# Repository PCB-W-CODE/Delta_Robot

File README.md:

# Delta_Robot
Design, simulation, and prototyping of a Delta robot with inverse kinematics, 3D printing, stepper motors, and manual control via joystick.

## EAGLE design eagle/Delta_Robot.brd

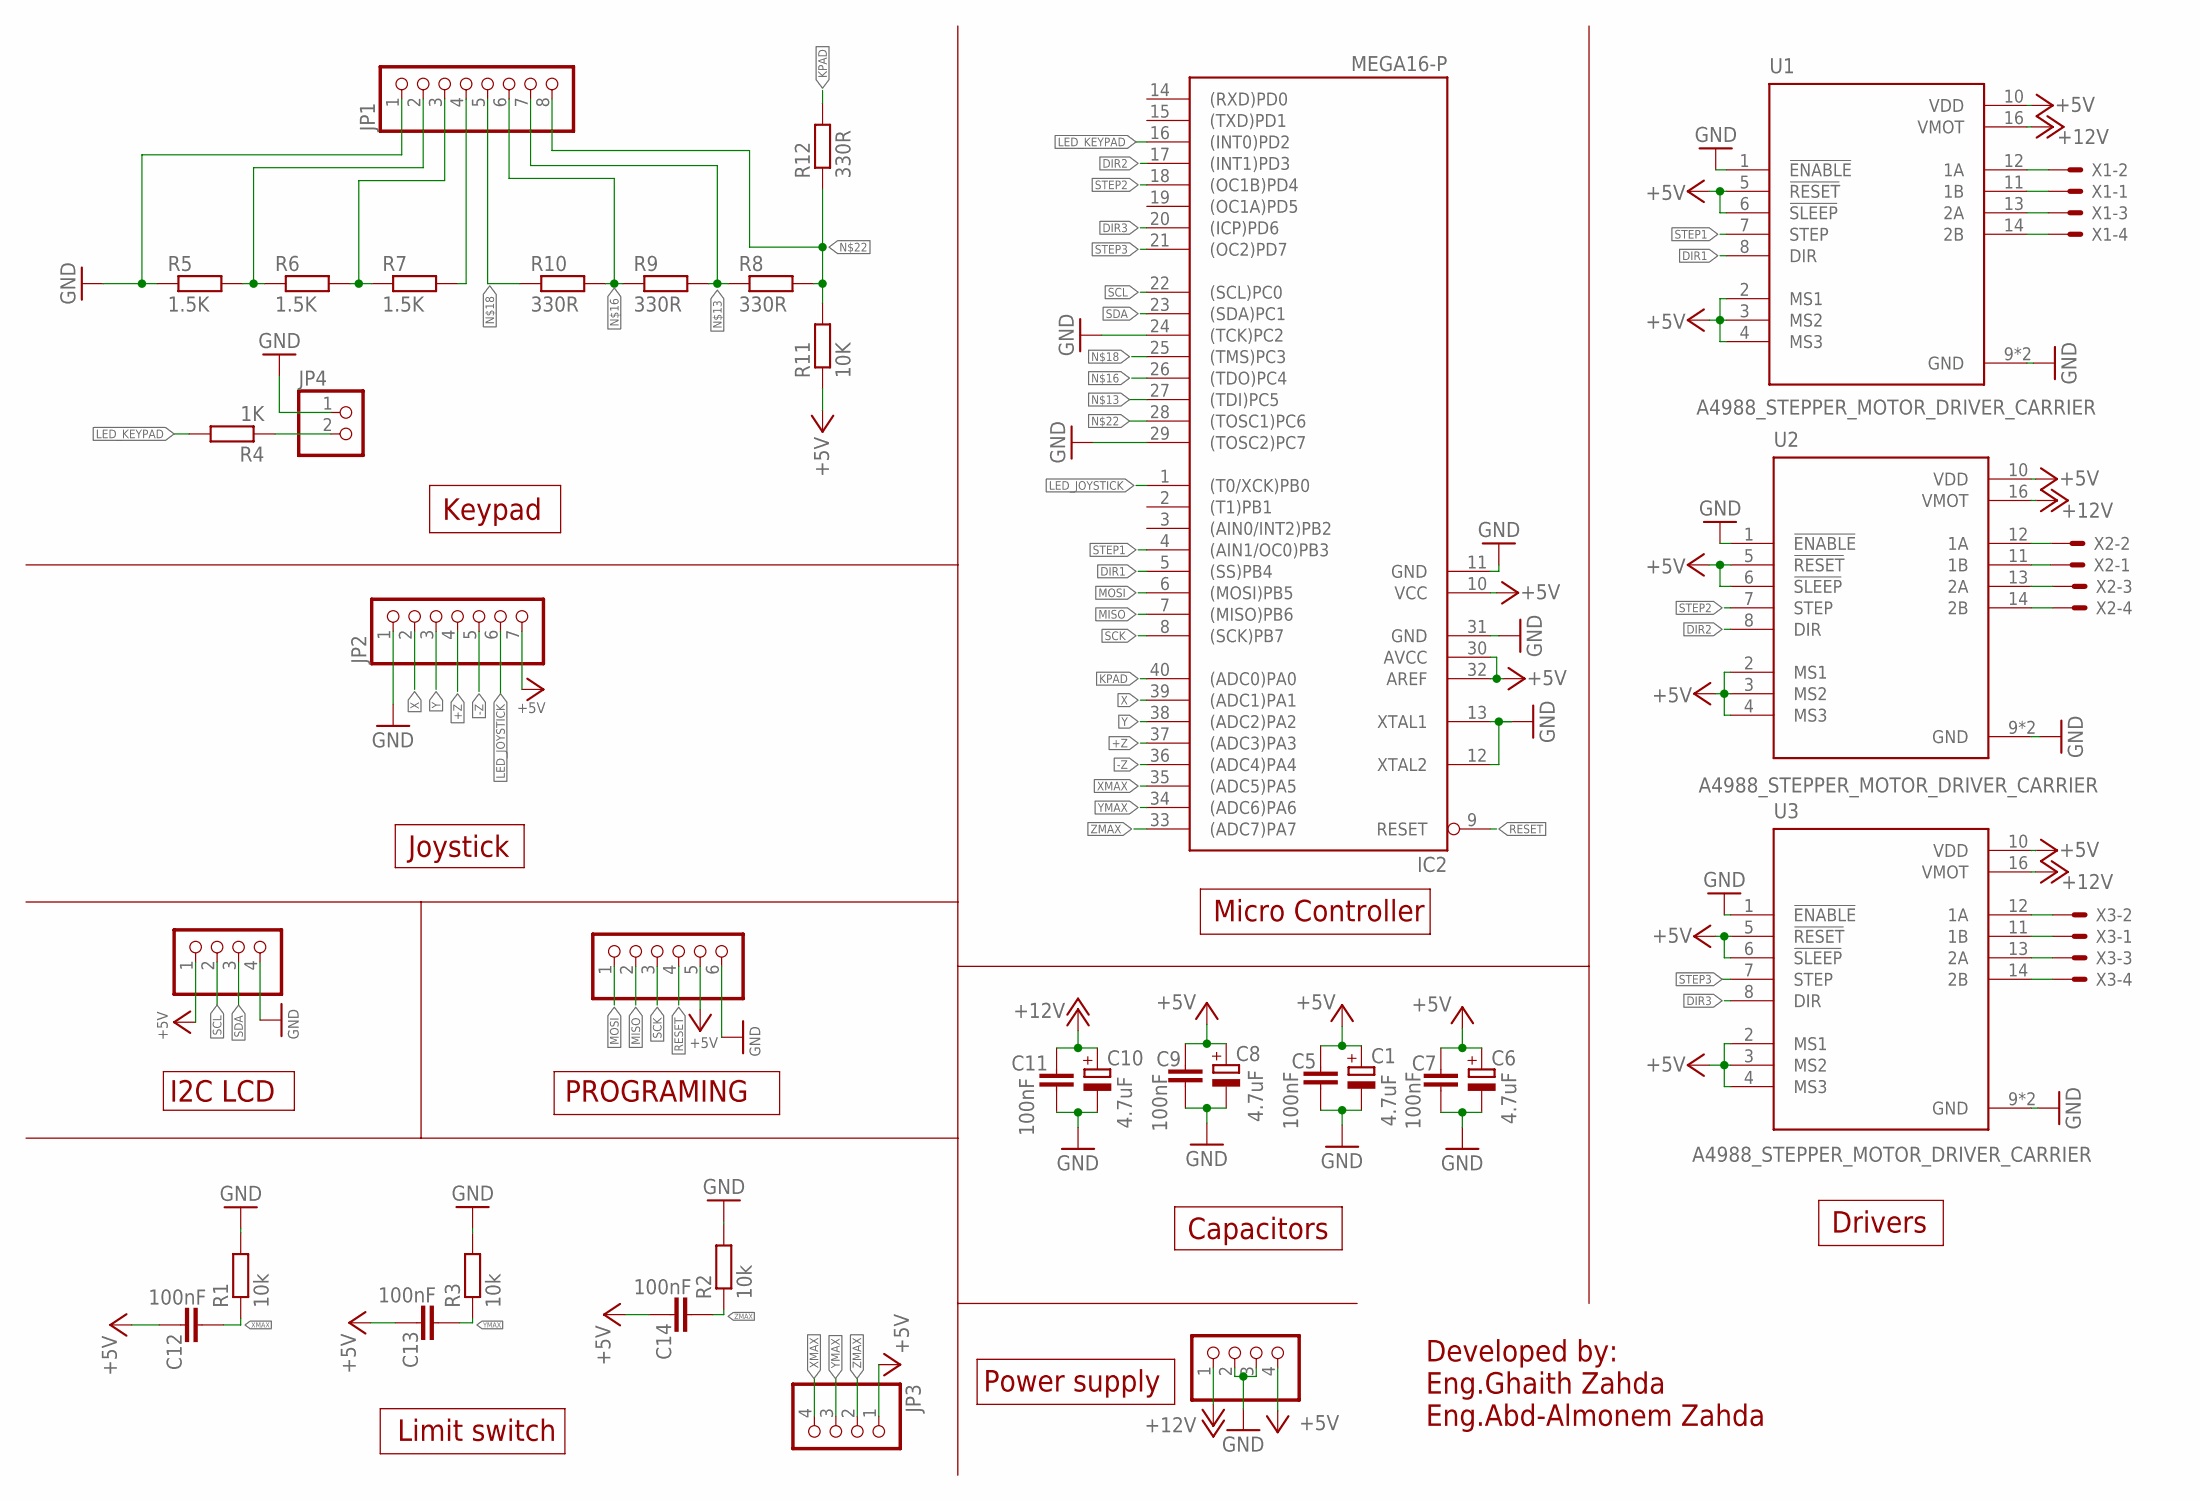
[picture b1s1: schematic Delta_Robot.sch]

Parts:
C1, C6, C8, C10: 4.7uF; E2,5-5
C5, C7, C9, C11, C12, C13, C14: 100nF; C025-024X044
I2C_LCD: PINHD-1X4; 1X04
IC2: MEGA16-P; DIL40
JP1: PINHD-1X8; 1X08
JP2: PINHD-1X7; 1X07
JP3: PINHD-1X4; 1X04
JP4: PINHD-1X2; 1X02
POWER: PINHD-1X4; 1X04
PROGRAMING: PINHD-1X6; 1X06
R1, R2, R3: 10k; 0204/5
R4: 1K; 0204/5
R5, R6, R7: 1.5K; 0204/5
R8, R9, R10, R12: 330R; 0204/5
R11: 10K; 0204/5
U1, U2, U3: A4988_STEPPER_MOTOR_DRIVER_CARRIER; MODULE_A4988_STEPPER_MOTOR_DRIVER_CARRIER
X1, X2, X3: JST-XH-04-PIN-LONG-PAD; JST-XH-04-PACKAGE-LONG-PAD

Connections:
+5V: C1.+, C5.2, C6.+, C7.2, C8.+, C9.2, C12.2, C13.2, C14.2, I2C_LCD.1, IC2.10 (VCC), IC2.30 (AVCC), IC2.32 (AREF), JP2.7, JP3.1, POWER.4, PROGRAMING.5, R11.1, U1.2 (MS1), U1.3 (MS2), U1.4 (MS3), U1.5 (!RESET), U1.6 (!SLEEP), U1.10 (VDD), U2.2 (MS1), U2.3 (MS2), U2.4 (MS3), U2.5 (!RESET), U2.6 (!SLEEP), U2.10 (VDD), U3.2 (MS1), U3.3 (MS2), U3.4 (MS3), U3.5 (!RESET), U3.6 (!SLEEP), U3.10 (VDD)
+12V: C10.+, C11.2, POWER.1, U1.16 (VMOT), U2.16 (VMOT), U3.16 (VMOT)
+Z: IC2.37 ((ADC3)PA3), JP2.4
-Z: IC2.36 ((ADC4)PA4), JP2.5
DIR1: IC2.5 ((SS)PB4), U1.8 (DIR)
DIR2: IC2.17 ((INT1)PD3), U2.8 (DIR)
DIR3: IC2.20 ((ICP)PD6), U3.8 (DIR)
GND: C1.-, C5.1, C6.-, C7.1, C8.-, C9.1, C10.-, C11.1, I2C_LCD.4, IC2.11 (GND), IC2.12 (XTAL2), IC2.13 (XTAL1), IC2.24 ((TCK)PC2), IC2.29 ((TOSC2)PC7), IC2.31 (GND), JP1.1, JP2.1, JP4.1, POWER.2, POWER.3, PROGRAMING.6, R1.2, R2.2, R3.2, R5.1, U1.1 (!ENABLE), U1.9 (GND), U1.15 (GND), U2.1 (!ENABLE), U2.9 (GND), U2.15 (GND), U3.1 (!ENABLE), U3.9 (GND), U3.15 (GND)
KPAD: IC2.40 ((ADC0)PA0), R12.2
LED_JOYSTICK: IC2.1 ((T0/XCK)PB0), JP2.6
LED_KEYPAD: IC2.16 ((INT0)PD2), R4.2
MISO: IC2.7 ((MISO)PB6), PROGRAMING.2
MOSI: IC2.6 ((MOSI)PB5), PROGRAMING.1
unnamed: JP4.2, R4.1
unnamed: U3.12 (1A), X3.2
unnamed: JP1.2, R5.2, R6.1
unnamed: U1.11 (1B), X1.1
unnamed: U1.12 (1A), X1.2
unnamed: U1.13 (2A), X1.3
unnamed: U1.14 (2B), X1.4
unnamed: U2.11 (1B), X2.1
unnamed: U2.12 (1A), X2.2
unnamed: U2.13 (2A), X2.3
unnamed: U2.14 (2B), X2.4
unnamed: U3.11 (1B), X3.1
unnamed: IC2.27 ((TDI)PC5), JP1.7, R8.1, R9.2
unnamed: U3.13 (2A), X3.3
unnamed: U3.14 (2B), X3.4
unnamed: IC2.26 ((TDO)PC4), JP1.6, R9.1, R10.2
unnamed: JP1.3, R6.2, R7.1
unnamed: IC2.25 ((TMS)PC3), JP1.5, R10.1
unnamed: JP1.4, R7.2
unnamed: IC2.28 ((TOSC1)PC6), JP1.8, R8.2, R11.2, R12.1
RESET: IC2.9 (RESET), PROGRAMING.4
SCK: IC2.8 ((SCK)PB7), PROGRAMING.3
SCL: I2C_LCD.2, IC2.22 ((SCL)PC0)
SDA: I2C_LCD.3, IC2.23 ((SDA)PC1)
STEP1: IC2.4 ((AIN1/OC0)PB3), U1.7 (STEP)
STEP2: IC2.18 ((OC1B)PD4), U2.7 (STEP)
STEP3: IC2.21 ((OC2)PD7), U3.7 (STEP)
X: IC2.39 ((ADC1)PA1), JP2.2
XMAX: C12.1, IC2.35 ((ADC5)PA5), JP3.4, R1.1
Y: IC2.38 ((ADC2)PA2), JP2.3
YMAX: C13.1, IC2.34 ((ADC6)PA6), JP3.3, R3.1
ZMAX: C14.1, IC2.33 ((ADC7)PA7), JP3.2, R2.1

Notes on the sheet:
Micro Controller
Drivers
Capacitors
Power supply
Limit switch
PROGRAMING
I2C LCD
Joystick
Keypad
Developed by: Eng.Ghaith Zahda Eng.Abd-Almonem Zahda

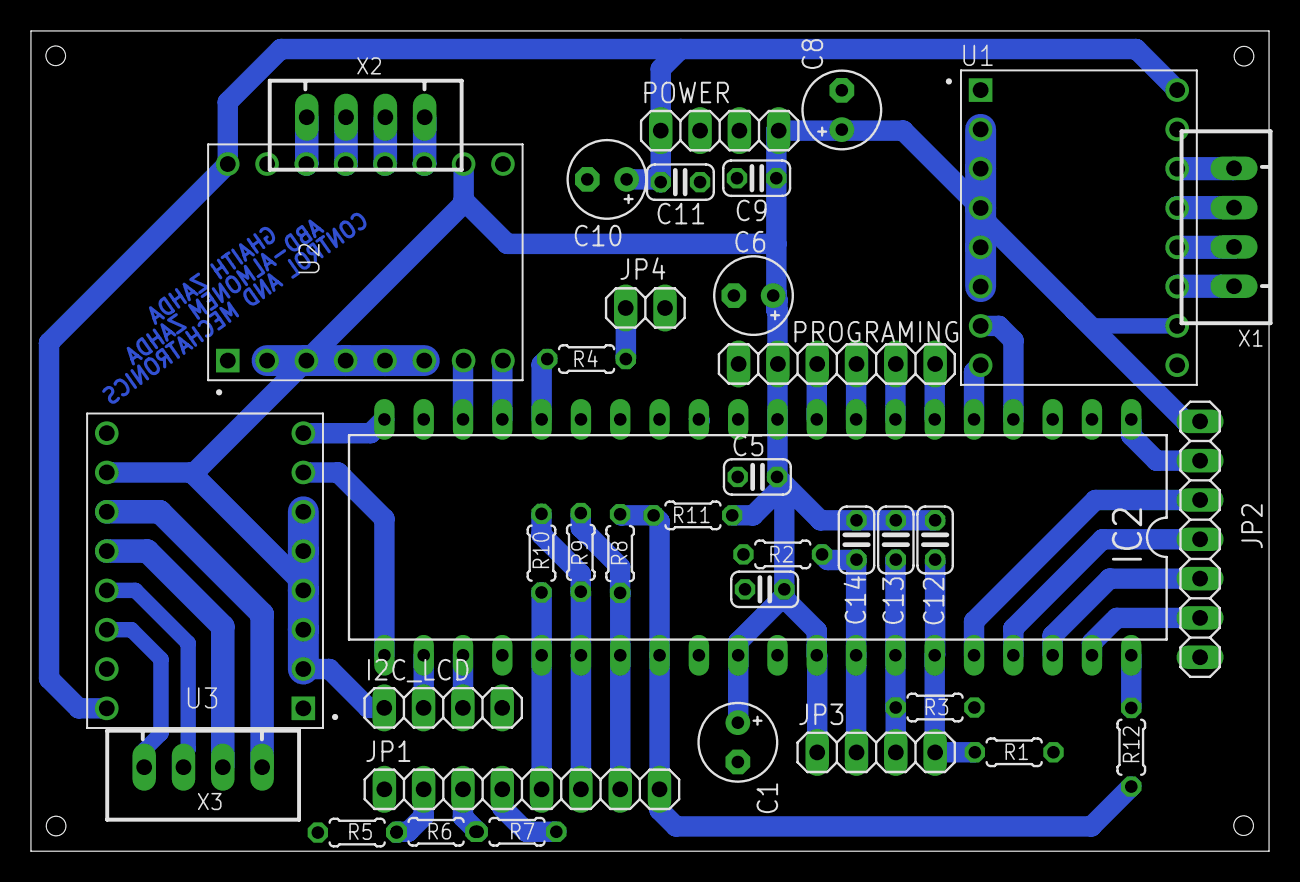
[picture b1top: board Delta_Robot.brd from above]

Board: 2 copper layers, 80.0 x 53.0 mm, 37 parts (0 on the bottom side), 45 nets.

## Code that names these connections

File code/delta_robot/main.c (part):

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#include "twi.h"
#include "twi_lcd.h"

#define LED_KEYPAD PD2
#define LED_JOYSTICK PB0
#define DIR1 PB4
#define DIR2 PD3
#define DIR3 PD6
#define StepMotor1 PB3
#define StepMotor2 PD4
#define StepMotor3 PD7
#define Z_Inc PA3
#define Z_Dec PA4
#define xMax PA5
#define yMax PA6
#define zMax PA7


// -------------------Global Variables--------------------
int step1 = 0, step2 = 0, step3 = 0;  // The number of steps to move
int degreesMotor1 = 0, degreesMotor2 = 0, degreesMotor3 = 0 // Angle motors=(degreesMotor/2)*0.1125
	,speedMotor1,speedMotor2,speedMotor3; // Speed motors
int theta_1=9999,theta_2=9999,theta_3=9999; // Target angle
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//------------------interrupt timer0---------------------
ISR(TIMER0_COMP_vect) {
	if (degreesMotor1 != theta_1) {
		if ((PINB &(1 << DIR1))) degreesMotor1++;
		else degreesMotor1--;
		PORTB ^= (1 << StepMotor1);
	}
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ISR(TIMER1_OVF_vect) {
	TCNT1=255-OCR1A+65280;
	if (degreesMotor2 != theta_2) {
		if ((PIND &(1 << DIR2))) degreesMotor2++;
		else degreesMotor2--;
		PORTD ^= (1 << StepMotor2);
	}
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//------------------interrupt timer2------------------
ISR(TIMER2_COMP_vect) {
	if (degreesMotor3 != theta_3) {
		if ((PIND &(1 << DIR3))) degreesMotor3++;
		else degreesMotor3--;
		PORTD ^= (1 << StepMotor3);
	}
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	twi_lcd_cmd(0x90);
	twi_lcd_msg(" limit switches ");
	while(degreesMotor1!=1702 || degreesMotor2!=1702 || degreesMotor3!=1702) {
		if(PINA &(1 << xMax)) {
			theta_1=1702;
			degreesMotor1=1702;
		}
		if(PINA &(1 << yMax)) {
			theta_2=1702;
			degreesMotor2=1702;
		}
		if(PINA &(1 << zMax)) {
			theta_3=1702;
			degreesMotor3=1702;
		}
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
